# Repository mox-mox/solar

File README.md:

# solar

This repo will contain the files for a step-up converter board for powering my laptop from some solar cells.

Idea
====

Create a power supply that can power my laptop for off-grid use. To avoid having to re-charge the supply and avoid charge limits, use solar cells*. The panel should be foldable in some way to be portable when hiking.

*: Additional bonus: When I have to turn the display backlight higher on [very] bright days, the solar cells will also produce more energy.

Specification
-------------
Board:
 - Input: ca. 6-15V, up to 10A DC from solar cells or a battery AND 20V from a Thinkpad power plug*.
 - Output0: 20V, 2.5A OR 3.0A Voltage for Thinkpad
 - Output1: 5V, 1.5A for charging my mobile phone
 - Output2: 3.3V, 2A for supplying miscellaneous electronic devices [optional]
 - Output4: Battery charger for lead acid car starter battery [optional] AND/OR charging circuit for a lithium polymer battery.

Power supply:
 - Use 16 highly efficient soloar cells of 15 by 15 centimeters, yielding about 9V at 1 to 6A
 - The cell array should be foldable in some way to allow handy transportation in a backpack

Case:
 - The case should hold the converter board and provide a protected space for the solar cells for transportation
 - Target size is about 16 by 20 by 5 centimeters
 - Will probably be made of steel sheets for maximum protection

Connectors:
 - Power connector for the solar cells or battery
 - Thinkpad compatible receptable to attach a Thinkpad power plug.
 - Thinkpad compatible power plug to supply the Laptop
 - Some USB ports to charge USB-devices
 - A multi-plug with exchangable tips for all kinds of devices
 - Pinheaders providing 3.3V

*The 20V will be looped through with the voltage regulator for output0 disabled. This way, the board can still provide the low-voltage outputs.

Soldering QFN and VSON packages
-------------------------------
 - The outer QFN 'pins' can be soldered from the outside, pre-tinning the pads and using [lots of] flux
 - The bottom pad will be soldered from below, unsing the thermal vias that are anyways needed. For that purpose, the solder resist mask is removed from these vias.
 - See: https://www.youtube.com/watch?v=d-f-SBC0GrU

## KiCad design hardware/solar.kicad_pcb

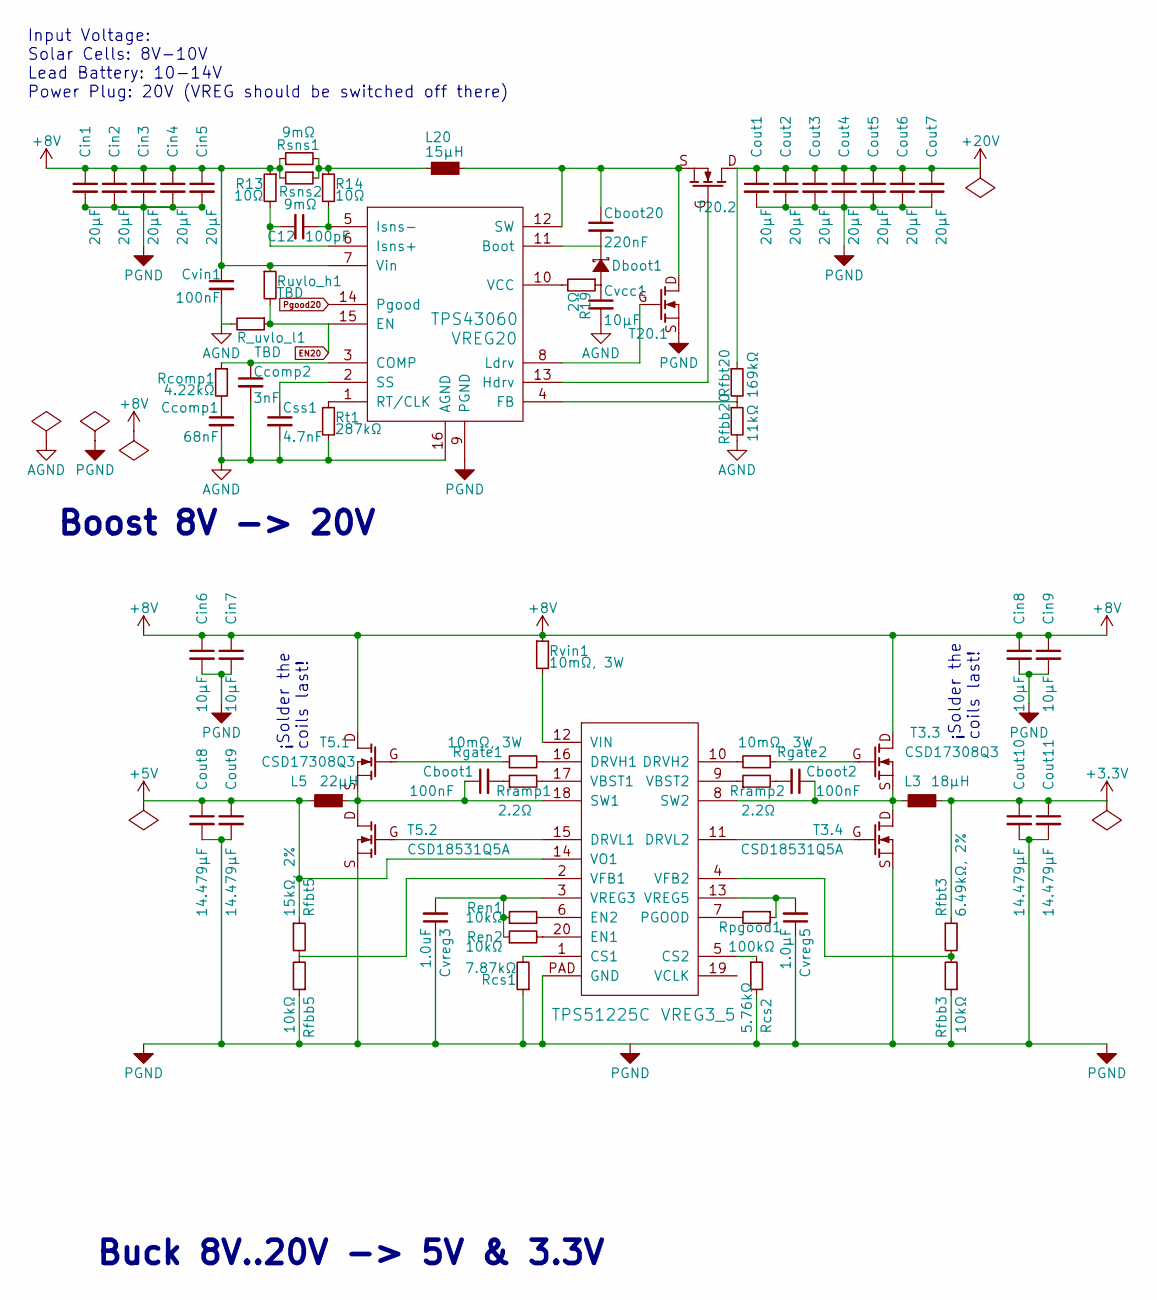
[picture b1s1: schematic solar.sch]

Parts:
C12: 100pF; C_0603_HandSoldering
Cboot1, Cboot2: 100nF; C_0603_HandSoldering
Cboot20: 220nF; C_0603_HandSoldering
Ccomp1: 68nF; C_0603_HandSoldering
Ccomp2: 3nF; C_0603_HandSoldering
Cin1, Cin2, Cin3, Cin4, Cin5: 20µF; C_1210_HandSoldering
Cin6, Cin7, Cin8, Cin9: 10µF; C_1210_HandSoldering
Cout1, Cout2, Cout3, Cout4, Cout5, Cout6, Cout7: 20µF; C_1210_HandSoldering
Cout8, Cout9, Cout10, Cout11: 14.479µF; C_1210_HandSoldering
Css1: 4.7nF; C_0603_HandSoldering
Cvcc1: 10µF; C_0805_HandSoldering
Cvin1: 100nF; C_0603_HandSoldering
Cvreg3: 1.0uF; C_0603_HandSoldering
Cvreg5: 1.0µF; C_0603_HandSoldering
Dboot1: ON Semiconductor MBRS2040LT3G; SMB_Handsoldering
L3: 18µH; Bourns_SRR1260_Series
L5: 22µH; Bourns_SRR1260_Series
L20: 15µH; Coilcraft_SER2900_Series
R13, R14: 10Ω; R_0603_HandSoldering
R19: 2Ω; R_0603_HandSoldering
R_uvlo_l1: TBD; R_0603_HandSoldering
Rcomp1: 4.22kΩ; R_0603_HandSoldering
Rcs1: 7.87kΩ; R_0603_HandSoldering
Rcs2: 5.76kΩ; R_0603_HandSoldering
Ren1, Ren2: 10kΩ; R_0603_HandSoldering
Rfbb3, Rfbb5: 10kΩ; R_0603_HandSoldering
Rfbb20: 11kΩ; R_0603_HandSoldering
Rfbt3: 6.49kΩ, 2%; R_0603_HandSoldering
Rfbt5: 15kΩ, 2%; R_0603_HandSoldering
Rfbt20: 169kΩ; R_0603_HandSoldering
Rgate1, Rgate2: 10mΩ, 3W; R_0603_HandSoldering
Rpgood1: 100kΩ; R_0603_HandSoldering
Rramp1, Rramp2: 2.2Ω; R_0603_HandSoldering
Rsns1, Rsns2: 9mΩ; R_1206_HandSoldering
Rt1: 287kΩ; R_0603_HandSoldering
Ruvlo_h1: TBD; R_0603_HandSoldering
Rvin1: 10mΩ, 3W; R_0805_HandSoldering
T3.3, T5.1: CSD17308Q3; VSON8_33x33
T3.4, T5.2: CSD18531Q5A; VSON8_50x60
T20.1: CSD17506Q5A; VSON8_50x60
T20.2: CSD17577Q5A; VSON8_50x60
VREG3_5: TPS51225C; QFN-20-1EP_3x3mm_Pitch0.4mm
VREG20: TPS43060; QFN-16-1EP_3x3mm_Pitch0.5mm

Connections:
+3V3: Cout10.1, Cout11.1, L3.2, Rfbt3.1
+5V: Cout8.1, Cout9.1, L5.2, Rfbt5.1, VREG3_5.14 (VO1)
+8V: Cin1.1, Cin2.1, Cin3.1, Cin4.1, Cin5.1, Cin6.1, Cin7.1, Cin8.1, Cin9.1, Cvin1.1, R13.1, Rsns1.1, Rsns2.2, Ruvlo_h1.1, Rvin1.1, T3.3.D, T5.1.D, VREG20.7 (Vin)
+20V: Cout1.1, Cout2.1, Cout3.1, Cout4.1, Cout5.1, Cout6.1, Cout7.1, Rfbt20.1, T20.2.D
AGND: Ccomp1.2, Ccomp2.2, Css1.2, Cvcc1.2, Cvin1.2, R_uvlo_l1.2, Rfbb20.2, Rt1.2, VREG20.16 (AGND), VREG20.17 (PowerPad)
EN20: R_uvlo_l1.1, Ruvlo_h1.2, VREG20.15 (EN)
unnamed: C12.1, R14.2, VREG20.5 (Isns-)
unnamed: C12.2, R13.2, VREG20.6 (Isns+)
unnamed: Cboot1.1, L5.1, T5.1.S, T5.2.D, VREG3_5.18 (SW1)
unnamed: Cboot1.2, Rramp1.1
unnamed: Cboot2.1, L3.1, T3.3.S, T3.4.D, VREG3_5.8 (SW2)
unnamed: Cboot2.2, Rramp2.2
unnamed: Cboot20.1, L20.2, T20.1.D, T20.2.S, VREG20.12 (SW)
unnamed: Cboot20.2, Dboot1.C, VREG20.11 (Boot)
unnamed: Ccomp1.1, Rcomp1.2
unnamed: Ccomp2.1, Rcomp1.1, VREG20.3 (COMP)
unnamed: Css1.1, VREG20.2 (SS)
unnamed: Cvcc1.1, Dboot1.A, R19.1
unnamed: Cvreg3.2, Ren1.1, Ren2.1, VREG3_5.3 (VREG3)
unnamed: Cvreg5.2, Rpgood1.1, VREG3_5.13 (VREG5)
unnamed: L20.1, R14.1, Rsns1.2, Rsns2.1
unnamed: R19.2, VREG20.10 (VCC)
unnamed: Rcs1.2, VREG3_5.1 (CS1)
unnamed: Rcs2.1, VREG3_5.5 (CS2)
unnamed: Ren1.2, VREG3_5.6 (EN2)
unnamed: Ren2.2, VREG3_5.20 (EN1)
unnamed: Rfbb3.2, Rfbt3.2, VREG3_5.4 (VFB2)
unnamed: Rfbb5.2, Rfbt5.2, VREG3_5.2 (VFB1)
unnamed: Rfbb20.1, Rfbt20.2, VREG20.4 (FB)
unnamed: Rgate1.1, T5.1.G
unnamed: Rgate1.2, VREG3_5.16 (DRVH1)
unnamed: Rgate2.1, T3.3.G
unnamed: Rgate2.2, VREG3_5.10 (DRVH2)
unnamed: Rpgood1.2, VREG3_5.7 (PGOOD)
unnamed: Rramp1.2, VREG3_5.17 (VBST1)
unnamed: Rramp2.1, VREG3_5.9 (VBST2)
unnamed: Rt1.1, VREG20.1 (RT/CLK)
unnamed: Rvin1.2, VREG3_5.12 (VIN)
unnamed: T3.4.G, VREG3_5.11 (DRVL2)
unnamed: T5.2.G, VREG3_5.15 (DRVL1)
unnamed: T20.1.G, VREG20.8 (Ldrv)
unnamed: T20.2.G, VREG20.13 (Hdrv)
PGND: Cin1.2, Cin2.2, Cin3.2, Cin4.2, Cin5.2, Cin6.2, Cin7.2, Cin8.2, Cin9.2, Cout1.2, Cout2.2, Cout3.2, Cout4.2, Cout5.2, Cout6.2, Cout7.2, Cout8.2, Cout9.2, Cout10.2, Cout11.2, Cvreg3.1, Cvreg5.1, Rcs1.1, Rcs2.2, Rfbb3.1, Rfbb5.1, T3.4.S, T5.2.S, T20.1.S, VREG3_5.PAD (GND), VREG20.9 (PGND)
Pgood20: VREG20.14 (Pgood)

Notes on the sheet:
Boost 8V -> 20V
Input Voltage: Solar Cells: 8V-10V Lead Battery: 10-14V Power Plug: 20V (VREG should be switched off there)
Buck 8V..20V -> 5V & 3.3V
¡Solder the coils last!

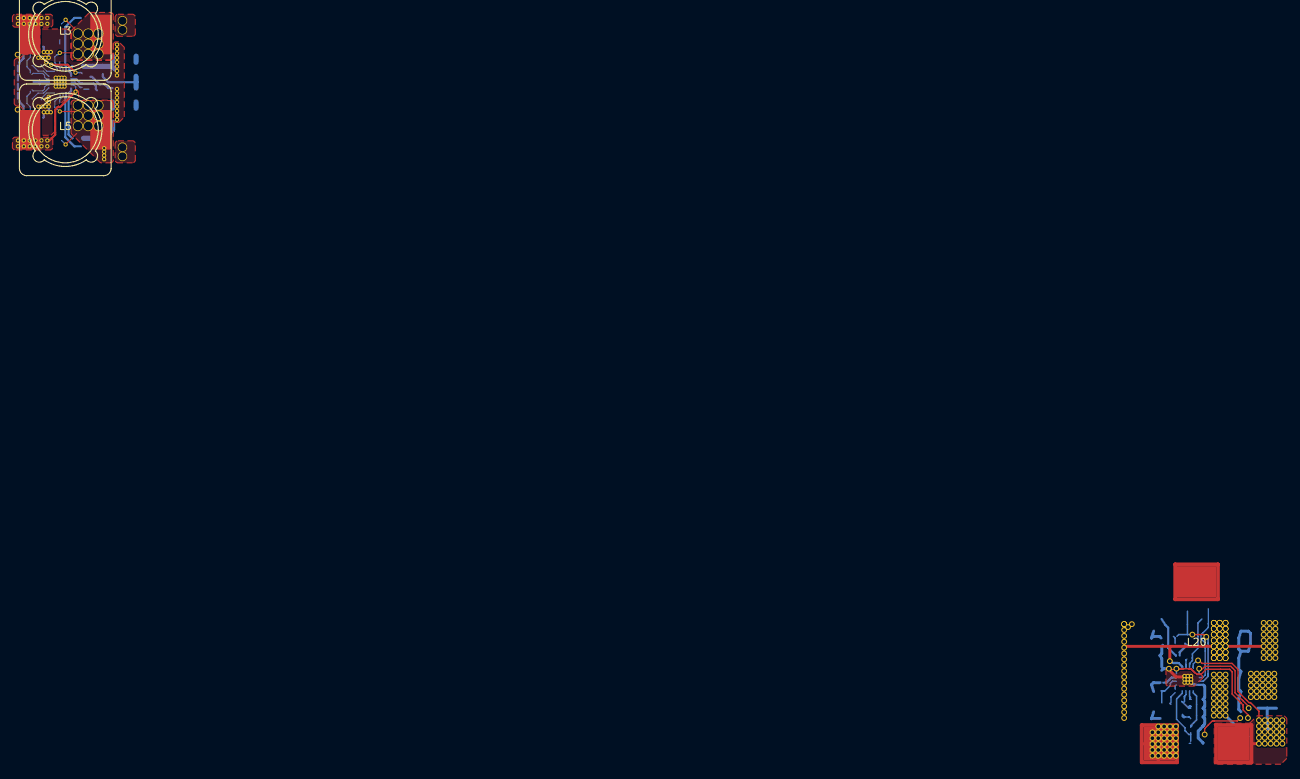
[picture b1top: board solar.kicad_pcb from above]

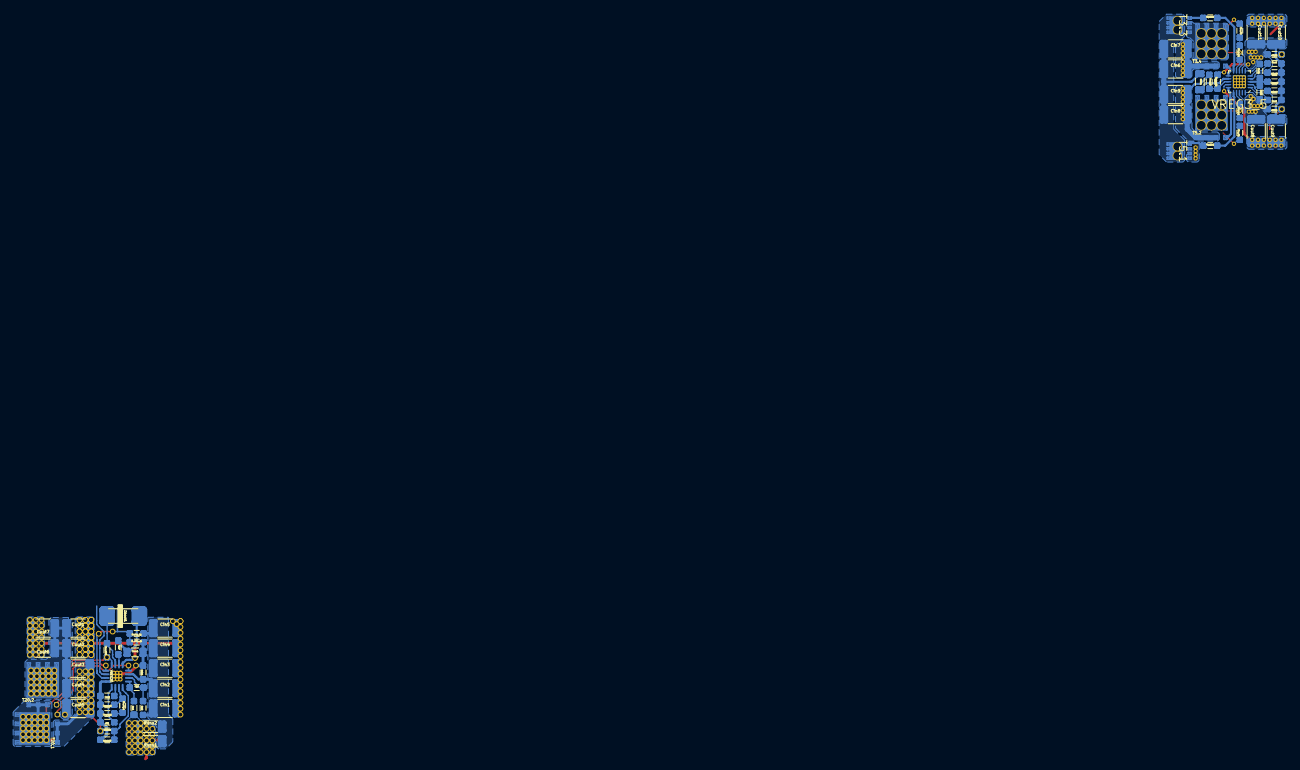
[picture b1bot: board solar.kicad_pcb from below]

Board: 2 copper layers, 68 parts (65 on the bottom side), 43 nets.

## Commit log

2016-04-05 Adding the TI Webbench design reports
2016-04-05 Adding the first attempts at kicad.
2016-04-05 Restarting that project with a clean state to avoid possible hickups from my trials with getting to know Kicad.
2016-04-05 Doing the schematic for VREG20.
2016-04-05 Adding datasheets.
2016-04-05 Finished schematic for VREG20.
2016-04-06 Adding more datasheets.
2016-04-06 Going to split PGND and AGND.
2016-04-06 Added missing resistor.
2016-04-06 Some progress around VREG20.
2016-04-07 Working on the VREG20.
2016-04-07 Working on the VREG20 (2).
2016-04-07 Added the UVLO resistors to VREG20.
2016-04-10 foobar
2016-04-11 Uptdating the footprints with the rounded-edges version.
2016-04-11 Changed the footprints to the rounded-corner-version.
2016-04-11 Tricky routing above VREG20.
2016-04-12 Updating VREG20 to be able to operate from up to 15V and deliver up to 3A (60W).
2016-04-12 Fixed wrong pad number in the VREG20 transistors.
2016-04-12 WIP: Adding fill polygons.
2016-04-12 Updating README
2016-04-12 Regenerated the voltage regulator circuits to allow operation from a 12V car starter battery.
2016-04-14 Adding VREG3_5 and surrounding chicken food.
2016-04-14 Beginning to assign footprints to the components of VREG5_3.
2016-10-07 Adding the second VREG
2016-10-07 Adding missing datasheets
2016-10-07 sorting the parts for the second VREG
2016-10-08 Moved the input capacitors
2016-10-08 Placing the coils
2016-10-08 Added two dummy resistors to avoid via for bridge.
2016-10-08 crash
2016-10-09 Progress with the layout.
2016-10-09 Routing progress.
2016-10-09 Some progress. Started to add vias.
2016-10-09 Adding polygons.
2016-10-09 More polygons.
2016-10-10 polys und stitches.
2016-10-10 Added solder vias for the big transistors of the buck.
2016-10-10 Replacing the big vias with smaller ones to solder like https://www.youtube.com/watch?v=d-f-SBC0GrU
